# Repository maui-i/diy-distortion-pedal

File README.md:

# DIY Distortion Pedal

A beginner-friendly guitar distortion pedal based on the classic MXR Distortion+ circuit: one op-amp, two germanium diodes, two knobs (**Gain** and **Level**), true bypass and an LED. About 20 parts and $15–30.

This repo has everything to build it:

- a step-by-step guide that starts on a solderless breadboard,
- a KiCad schematic,
- a ready-to-order printed circuit board (PCB),
- a wiring diagram for the jacks, footswitch and power.

| PCB (3D render) | Schematic |
| --- | --- |
|  |  |

## Three ways to build it

| Path | Soldering | Good for | Start here |
| --- | --- | --- | --- |
| **1. Breadboard** | Only the jack wires | Hearing it work in an afternoon, trying mods | [Build guide, parts 1–2](docs/build-guide.md#step-by-step-part-1-build-it-on-a-breadboard) |
| **2. Perfboard** | Yes | Making the breadboard version permanent, no PCB order needed | [Build guide, part 3](docs/build-guide.md#step-by-step-part-3-make-it-permanent) |
| **3. Custom PCB** | Yes, easiest of the soldered options | A tidy, quiet pedal that fits a 1590B box | [PCB build guide](docs/pcb-build.md) |

Whichever path you take, building the breadboard version first is the best way to learn the circuit and to check your parts.

## What's in the repo

```
docs/
  build-guide.md          Full beginner guide: parts, tools, breadboard, perfboard, troubleshooting, mods
  pcb-build.md            Ordering and assembling the PCB, off-board wiring
  how-it-works.md         The circuit explained, with the numbers behind each part
  images/                 Schematic, PCB renders, assembly view, wiring diagram
hardware/
  schematic.pdf           Printable schematic
  kicad/                  KiCad 10 project (schematic, PCB, project libraries)
  fabrication/
    diy-distortion-pedal-gerbers.zip   Upload this to a PCB maker
    bom.csv                            Bill of materials exported from the schematic
    assembly-top.pdf                   Printable parts placement
tools/                    Scripts that generated and check the design (see tools/README.md)
```

## The circuit at a glance

Guitar → input jack → footswitch → **gain stage** (TL071 op-amp, up to about 214× with the GAIN knob) → **clipping** (two 1N34A germanium diodes) → **LEVEL** knob → footswitch → output jack → amp.

It runs on a 9 V battery or a standard 9 V center-negative pedal supply and draws only a few milliamps. Read [how it works](docs/how-it-works.md) for the details.

## PCB at a glance

- 50 × 48 mm, 2 layers, all through-hole parts, no vias
- Pots mount on the back of the board so their shafts go through the enclosure lid
- Clearly labelled pads for IN, OUT, 9V, GND and LED+
- Design checks pass: KiCad ERC and DRC show 0 errors, and the board matches the schematic

## Safety

9 V DC only, never mains power. Treat the soldering iron with respect, and turn your amp down before plugging anything in. See the [safety section](docs/build-guide.md#safety) of the guide.

## License

MIT, see [LICENSE](LICENSE). The Distortion+ circuit itself is a decades-old classic that's widely documented; this repo's guide, drawings and PCB layout are original.

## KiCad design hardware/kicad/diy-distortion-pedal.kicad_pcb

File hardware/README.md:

# Hardware

| Path | What it is |
| --- | --- |
| `schematic.pdf` | Printable schematic (A4). |
| `kicad/diy-distortion-pedal.kicad_pro` | KiCad project. Open this in KiCad 10 or newer. |
| `kicad/diy-distortion-pedal.kicad_sch` | Schematic, including the off-board wiring (jacks, footswitch, DC jack, battery, LED). Those parts are marked "not on board" so they appear in the BOM but not on the PCB. |
| `kicad/diy-distortion-pedal.kicad_pcb` | PCB layout. |
| `kicad/pedal.kicad_sym` | Project symbol: `SW_3PDT`, a 9-lug footswitch whose pin numbers match the build guide's lug numbering. |
| `kicad/pedal.pretty/Pot_16mm_PCB.kicad_mod` | Project footprint: 16 mm PCB-mount pot, legs at 5 mm pitch, 7.5 mm from the shaft. |
| `fabrication/diy-distortion-pedal-gerbers.zip` | Gerber and Excellon drill files, ready to upload to a PCB maker. |
| `fabrication/bom.csv` | Bill of materials exported from the schematic (all parts, on and off the board). |
| `fabrication/assembly-top.pdf` | Component-side silkscreen and copper, for placing parts. |

## Board specs

| | |
| --- | --- |
| Size | 50 × 48 mm, 2 mm corner radius |
| Layers | 2, 1.6 mm FR-4, ground pour on both sides |
| Tracks | 0.4 mm signal, 0.7 mm for +9V, VIN and GND; 0.25 mm clearance |
| Holes | 0.8–1.2 mm plated, no vias |
| Parts | All through-hole; pots on the back, everything else on the front |

## Checks

All of these pass with zero errors or warnings, and `tools/export.sh` re-runs them:

- **ERC** (electrical rules check) on the schematic.
- **DRC** (design rules check) on the PCB: clearances, courtyards, silkscreen, unconnected pads.
- **Schematic parity**: the PCB's footprints and nets match the schematic.
- **Connection list**: `tools/check_netlist.py` compares the schematic's netlist with the connection list in `docs/build-guide.md` (including footswitch, jacks and power), so the PCB and the guide describe the same circuit.

## Editing

Open the `.kicad_pro` file in KiCad and edit as usual. After changes, run `tools/export.sh` from the repo root to refresh the Gerbers, BOM, PDFs and images. If you move parts, re-route by hand or with KiCad's router, then refill zones (press **B**) before exporting.

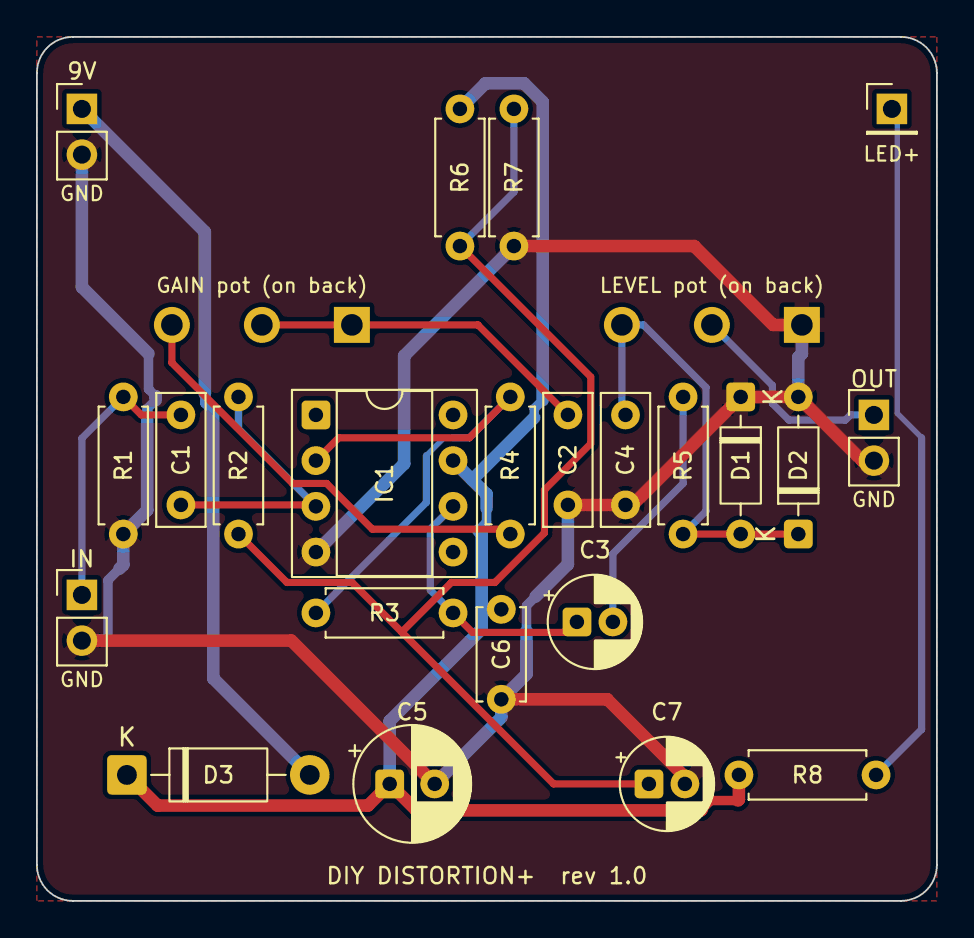
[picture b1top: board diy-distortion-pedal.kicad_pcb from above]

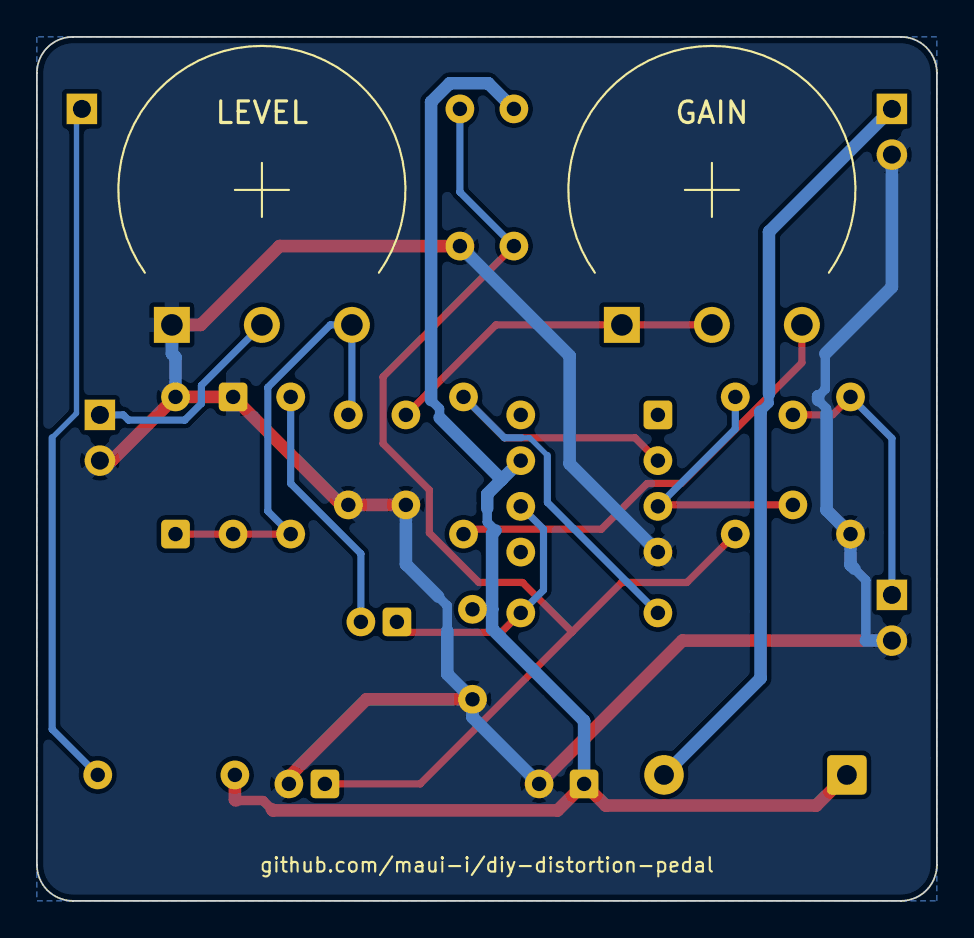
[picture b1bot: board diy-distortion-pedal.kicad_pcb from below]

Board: 2 copper layers, 50.0 x 48.0 mm, 25 parts (2 on the bottom side), 14 nets.

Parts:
C1: 10n; C_Rect_L7.2mm_W2.5mm_P5.00mm_FKS2_FKP2_MKS2_MKP2
C2: 47n; C_Rect_L7.2mm_W2.5mm_P5.00mm_FKS2_FKP2_MKS2_MKP2
C3: 1u; CP_Radial_D5.0mm_P2.00mm
C4: 1n; C_Rect_L7.2mm_W2.5mm_P5.00mm_FKS2_FKP2_MKS2_MKP2
C5: 100u; CP_Radial_D6.3mm_P2.50mm
C6: 100n; C_Disc_D5.0mm_W2.5mm_P5.00mm
C7: 10u; CP_Radial_D5.0mm_P2.00mm
D1, D2: 1N34A; D_DO-35_SOD27_P7.62mm_Horizontal
D3: 1N5817; D_DO-41_SOD81_P10.16mm_Horizontal
IC1: TL071; DIP-8_W7.62mm_Socket
J1: IN; PinHeader_1x02_P2.54mm_Vertical
J2: OUT; PinHeader_1x02_P2.54mm_Vertical
J3: 9V IN; PinHeader_1x02_P2.54mm_Vertical
J4: LED+; PinHeader_1x01_P2.54mm_Vertical
R1, R2, R3: 1M; R_Axial_DIN0207_L6.3mm_D2.5mm_P7.62mm_Horizontal
R4, R8: 4.7k; R_Axial_DIN0207_L6.3mm_D2.5mm_P7.62mm_Horizontal
R5: 10k; R_Axial_DIN0207_L6.3mm_D2.5mm_P7.62mm_Horizontal
R6, R7: 100k; R_Axial_DIN0207_L6.3mm_D2.5mm_P7.62mm_Horizontal
RV1: C1M (GAIN); Pot_16mm_PCB
RV2: A10K (LEVEL); Pot_16mm_PCB

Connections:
+9V: C5.1, C6.1, D3.1, IC1.7, R6.1, R8.1
/CLIP: C4.1, D1.2, D2.1, R5.2, RV2.3
/FX_IN: C1.1, J1.1, R1.1
/FX_OUT: J2.1, RV2.2
/LED_A: J4.1, R8.2
/VIN: D3.2, J3.1
/VREF: C7.1, R2.2, R6.2, R7.1
GND: C2.2, C4.2, C5.2, C6.2, C7.2, D1.1, D2.2, IC1.4, J1.2, J2.2, J3.2, R1.2, R7.2, RV2.1
unnamed: C2.1, RV1.1, RV1.2
unnamed: C3.1, IC1.6, R3.2
unnamed: C3.2, R5.1
unnamed: C1.2, IC1.3, R2.1
unnamed: IC1.2, R3.1, R4.1
unnamed: R4.2, RV1.3

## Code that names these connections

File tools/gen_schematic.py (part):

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          ref_at=(81.28, 101.6), val_at=(81.28, 104.14))
    place('C2', 'Device:C', '47n', 66.04, 107.95, 0, FP['Cfilm'])

    label('FX_IN', (40.64, y0), 180)
    wire((40.64, y0), (50.8, y0))
    junction((50.8, y0))
    wire((50.8, y0), P('R1', 1))
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    wire((170.18, yc), P('RV2', 3))
    for x in xs:
        junction((x, yc))
    label('CLIP', (160.02, yc), 0)
    wire((xs[0], yc), P('D1', 2))      # D1 anode to CLIP
    gnd(P('D1', 1))
    wire((xs[1], yc), P('D2', 1))      # D2 cathode to CLIP
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    gnd(P('RV2', 1))
    w2 = P('RV2', 2)
    wire(w2, (w2[0], 83.82), (177.8, 83.82))
    label('FX_OUT', (177.8, 83.82), 0)

    # ---------------- power
    ox = 10.16
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    gnd(P('R7', 2))
    gnd(P('C7', 2))
    wire(P('R8', 2), (127 + ox, yr + 15.24))
    label('LED_A', (127 + ox, yr + 15.24), 0)

    # ---------------- board connectors
    text('BOARD PADS', 20.32, 120.65, 2.0, True)
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    nc(P('SW1', 9, 3))
    a = P('D4', 2)
    wire(a, (a[0] + 5.08, a[1]))
    label('LED_A', (a[0] + 5.08, a[1]), 0)
    text('LED anode wires to pad J4 (R8 on the board limits the current).', 190.5, 104.14)

    text('POWER INPUT', 190.5, 113.03, 2.0, True)
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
